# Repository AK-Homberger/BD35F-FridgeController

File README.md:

# BD35F Fridge Controller
An electronic thermostat for a Danfoss/Secop [BD35F](https://assets.danfoss.com/documents/latest/178661/AI376451289296en-000101.pdf) Compressor with ESP8266 (D1 Mini).

The Danfoss/Secop BD35F compressor is a widely used DC powered compressor. I'm using it on my boat to cool the fridge. Unfortunately, the original thermostat was defect. Therfore, I decided to create an electronic alternative that has more features than the standard mechanical one.

## Features:
- Uses ESP8266 (D1 Mini) as processor.
- Dual language support (English/German).
- Easy upload of firmware without Arduino IDE possible.
- Temperature is measured with [DS18B20](https://encrypted-tbn0.gstatic.com/shopping?q=tbn:ANd9GcRNmu3D8hUJPGhuSA7nLRoa413b-gMmKO3SzPfPqZvY6wbsBIp207lLPlJ23y0RRw-2xIi-4CoqkTE98FSd--icjlcXm1W_YQ) sensor.
- Implements a Two-Point with I controller to increase the accuracy.
- Supports variable compressor speeds (2000 - 3500 RPM) to adjust cooling capacity and power consumption.
- Supports Boost function to cool down with more power.
- Supports automatic or manual Defrost routine.
- WLAN support (AP or client mode). Configurable via Wifi Manager.
- Browser interface and MDNS support (http://fridgecontrol.local).
- All parameters are configurable with a browser and stored in flash memory of ESP8266.
- [PCB](https://github.com/AK-Homberger/BD35F-FridgeController/blob/main/BD35F-FridgeController/BD35F-FridgeController-PCB.pdf) layout is available in repository (KiCad) and can be orderd from [Aisler.net](https://aisler.net/p/VBBOGMUR).

## Hardware
The hardware is based on an ESP8266 (D1 Mini) and a few additional parts. The 5 Volt supply voltage for the D1 Mini is created with a [step-down](https://www.reichelt.de/de/de/shop/produkt/dc_dc-wandler_r78e_5_v_500_ma_single-159161) converter. 
The temperature is measuered with a [DS18B20](https://www.analog.com/media/en/technical-documentation/data-sheets/ds18b20.pdf) sensor. The compressor is controlled with an open collector transistor between the connection T and C on the BD35F. 

The BD35F is measuering the current between T and C. C is on GND level and T has a pull-up resistor to 5 Volt. Only a few milliampere are flowing. A small NPN transitor (BC337) is sufficient here. There are two options: T permanently on GND level means 2000 RPM speed. A PWM signal (5 KHz) with a defined duty-cycle is used to set speeds from 2000 to 3500 RPM.

The PCB has three connectors:

### 1. Power 
Connect +/-to 12 Volt to the J1 connector. There is a protection against wrong cabling for +/-.

### 2. DS18B20 Temperature Sensor
Connect the three cables from the DS18B20 to the connector J2. The data line has already the pull-up resistor on the PCB. Red = VDD, Yello = D, Blue = GND.
Place the Sensor in the Fridge in middle highth.

### 3. BD35F Compressor
Connect J3 to the compressor connector. Remove the old thermostat cables and connect the cables C and  T to the compressor. You need appropriate cable shoes for the connection.

## Software
There are two ways to install the software to the D1 Mini. Either you install the Arduino IDE or you direcly flash the BIN-file to the device.

### Arduino IDE
Just [download](https://www.arduino.cc/en/software/) the IDE (version 2.x works well). Then add the Boad URL in preferences: "https://arduino.esp8266.com/stable/package_esp8266com_index.json" and install the Board software in the IDE. Then install the following libraries with the library manager:

- WiFiManager
- ArduinoJson
- OneWire
- DallasTemperature
- Preferences

Then download the sketch from GitHud (Button "Code" and download as ZIP) and extract it. Then move to the [FridgeControl.ino](https://github.com/AK-Homberger/BD35F-FridgeController/blob/main/FridgeControl/FridgeControl.ino) file and open the sketch.
Connect the D1 mini with an USB-Cable to the PC and upload the sketch to the D1 Mini. Later uploads can be done with the OTA function via network.

### NodeMCU-PyFlasher
This works without installation of the IDE. Simply download the [NodeMCU-PyFlasher](https://github.com/nodemcu/nodemcu-firmware/releases) and start it. 

Select appropriate serial port and then move to the bin file in the deownloaded code. Use the seetings as shown for the upload.

## Usage

After upload of the firmware you have to re-power the device to start the [Wifi-Manager](https://github.com/tzapu/WiFiManager) (within 2 minutes after restart). Just look for a new WLAN network with the name "Fridgeconfig_AP" and connect to it, without a password. The browser will start automatically. Then select the network (ssid) you want to connect to and enter the password. 

If you don't configure or press "Exit" the device remain in AP mode with a changed name "Fridgecontrol_AP".

You can use this to test the device without a real network to connect to. But this is an open connection. Don't use this permanently.

To start the web interface enter "http://fridgecontrol.local" in the browser. The interface looks then like this:

The page shows the current fridge temperature, the average temperature, the desired set temperature. Duty cycle shows the percentage of the on time compared to the last on and off time cycle. The values are also shown in minutes (On/Off). The status filed shows the staus of the controller (Auto, On, Off, Boost or Defrost).

With the slidebar and +/- you can modify the the set temperature.

With the buttons you can set the mode:

- Auto: Standard mode to control the temperature.
- ON: Switch on the compressor permanently.
- Off: Switch off the compressor permanently.
- Boost: Cool down for a defined time with a different set point, hysteresis and speed.
- Defrost: Manually start a defrost cycle.
- Set: Opens a settings page.

With the settings page you can control the behaviour of the controller without a need to recompile the code. The following settings are available:

- Language:   0=English 1=German language
- Hysteresis: Sets the Hysteresis/deviation for the two point controller. 2 means +/- 2 K. For a set temperature of 6 that means the temperature will between 4 and 8 degrees.
- RPM:         The desired speed of the compressor. Set as low as possible to reduce power consumption (2000 = 3,5A, 3500 = 7A). "0" means T permanently to GND and 2000 RPM (original mechanical thermostat behaviour).
- AVG Error:   This is the allowed deviation from the average. 0 means the compressor will cool down in every cycle until the average temperature reaches the set temperature. The average temperature is calculated with a low pass filter with K of 1/3600. Means average over about one hour.
- Max          High: The maximum high temperture. The compressor will be switched off, if ths level is reached. Independent of average temperature.
- Max Low:     The maximum low temperture. The compressor will be switched on, if ths level is reached. Independent of average temperature.
- Boost Temp.: Desired temperature for the boost function.
- Boost Hyst.: Hysteresis/deviation for the boost function.
- Boost Time   Time in minutes for the boost function.
- Boost RPM:   Compressor speed for the boost function.
- Max Runtime: Used to detect a needed defrost cycle. If the compressor runs for the defined time, a mandatory defrost cycle will start.
- Defrost Time: Set the time for the defrost cycle. Time depends on local fridge details.

After changes press the "Set" butten. The entered value will be checked against the allowed ranges. If everyting is OK you can use "Back" to go back to the main page.

# Parts
- PCB [Aisler](https://aisler.net/p/VBBOGMUR)
- U1 D1 Mini [Link](https://www.reichelt.de/de/en/d1-mini-esp8266-v3-0-d1-mini-p253978.html?&nbc=1)
- U2 Voltage regulator [Link](https://www.reichelt.de/de/de/shop/produkt/dc_dc-wandler_r78e_5_v_500_ma_single-159161)
- R1 Resistor 1 KOhm [Link](https://www.reichelt.de/de/en/carbon-film-resistor-1-4-w-5-1-0-kilo-ohms-1-4w-1-0k-p1315.html?&trstct=pos_2&nbc=1)
- R2 Resistor 4,7 KOhm [Link](https://www.reichelt.com/de/en/shop/product/carbon_film_resistor_1_4_w_5_4_7_kohm-1425)
- Q1 Transistor BC337 [Link](https://www.reichelt.de/de/en/transistor-to-92-bl-npn-45v-800ma-bc-337-25-dio-p219125.html?&nbc=1)
- D1 Diode 1N4001 [Link](https://www.reichelt.de/de/en/rectifier-diode-do41-50-v-1-a-1n-4001-p1723.html?&nbc=1)
- C1 Condensator 10µF [Link](https://www.reichelt.de/de/de/shop/produkt/tantal-kondensator_10_f_10_35v_rm_2_5-20334)
- J1/J3 Connector 2-pin (*2) [Link](https://www.reichelt.de/de/en/2-pin-terminal-strip-spacing-5-08-akl-101-02-p36605.html?&nbc=1)
- J2 Connector 3-pin [Link](https://www.reichelt.com/de/en/shop/product/3-pin_terminal_strip_spacing_5_08-36606)
- DS18B20 [Link](https://www.reichelt.com/de/en/shop/product/shelly_temperature_sensor_ds18b20-287127)

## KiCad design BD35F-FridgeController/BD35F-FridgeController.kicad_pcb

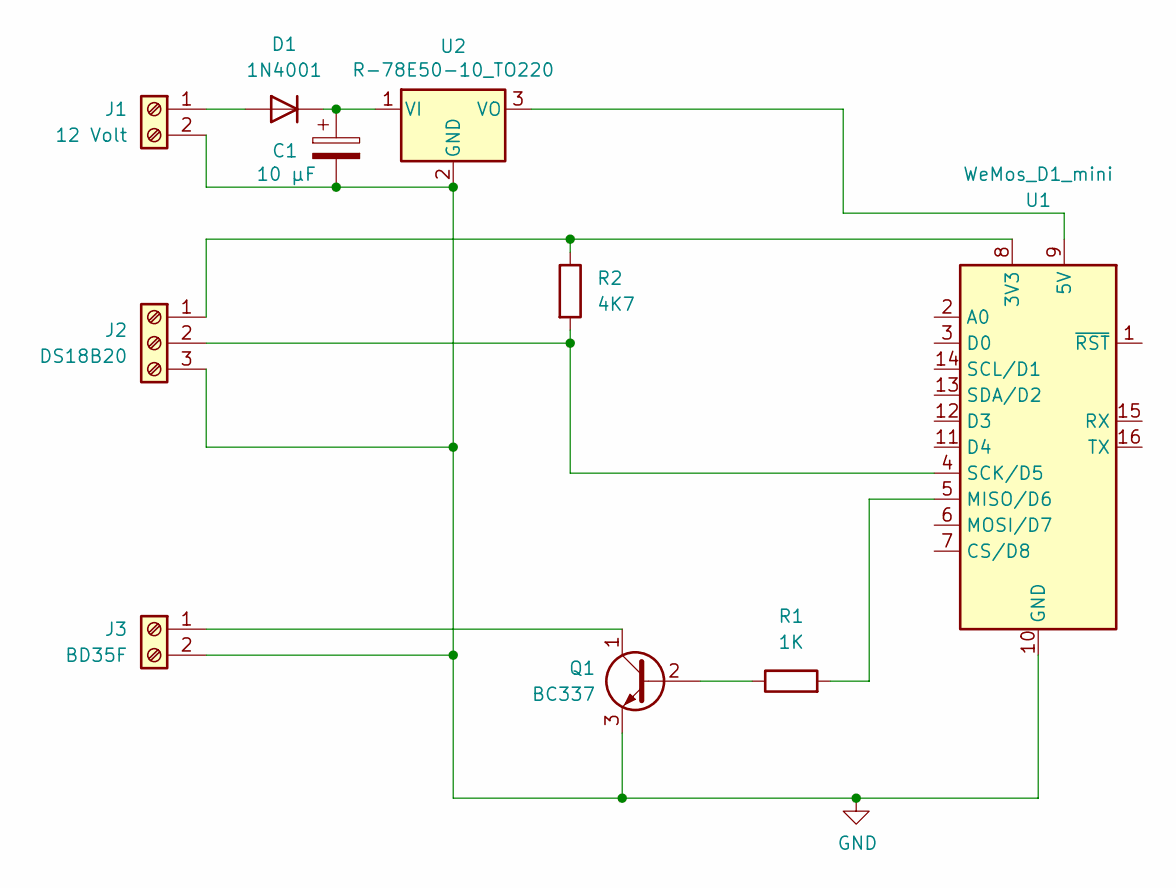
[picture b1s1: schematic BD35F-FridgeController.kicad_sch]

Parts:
C1: 10 µF; CP_Radial_D5.0mm_P2.50mm
D1: 1N4001; D_DO-41_SOD81_P10.16mm_Horizontal
J1: 12 Volt; TerminalBlock_bornier-2_P5.08mm
J2: DS18B20; TerminalBlock_bornier-3_P5.08mm
J3: BD35F; TerminalBlock_bornier-2_P5.08mm
Q1: BC337; TO-92_HandSolder
R1: 1K; R_Axial_DIN0207_L6.3mm_D2.5mm_P10.16mm_Horizontal
R2: 4K7; R_Axial_DIN0207_L6.3mm_D2.5mm_P10.16mm_Horizontal
U1: WeMos_D1_mini; WEMOS_D1_mini_light
U2: R-78E50-10_TO220; TO-220-3_Vertical

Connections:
GND: C1.2, J1.2, J2.3, J3.2, Q1.3 (E), U1.10 (GND), U2.2 (GND)
unnamed: D1.2 (A), J1.1
unnamed: C1.1, D1.1 (K), U2.1 (VI)
unnamed: J2.1, R2.1, U1.8 (3V3)
unnamed: J2.2, R2.2, U1.4 (SCK/D5)
unnamed: J3.1, Q1.1 (C)
unnamed: Q1.2 (B), R1.1
unnamed: U1.9 (5V), U2.3 (VO)
unnamed: R1.2, U1.5 (MISO/D6)

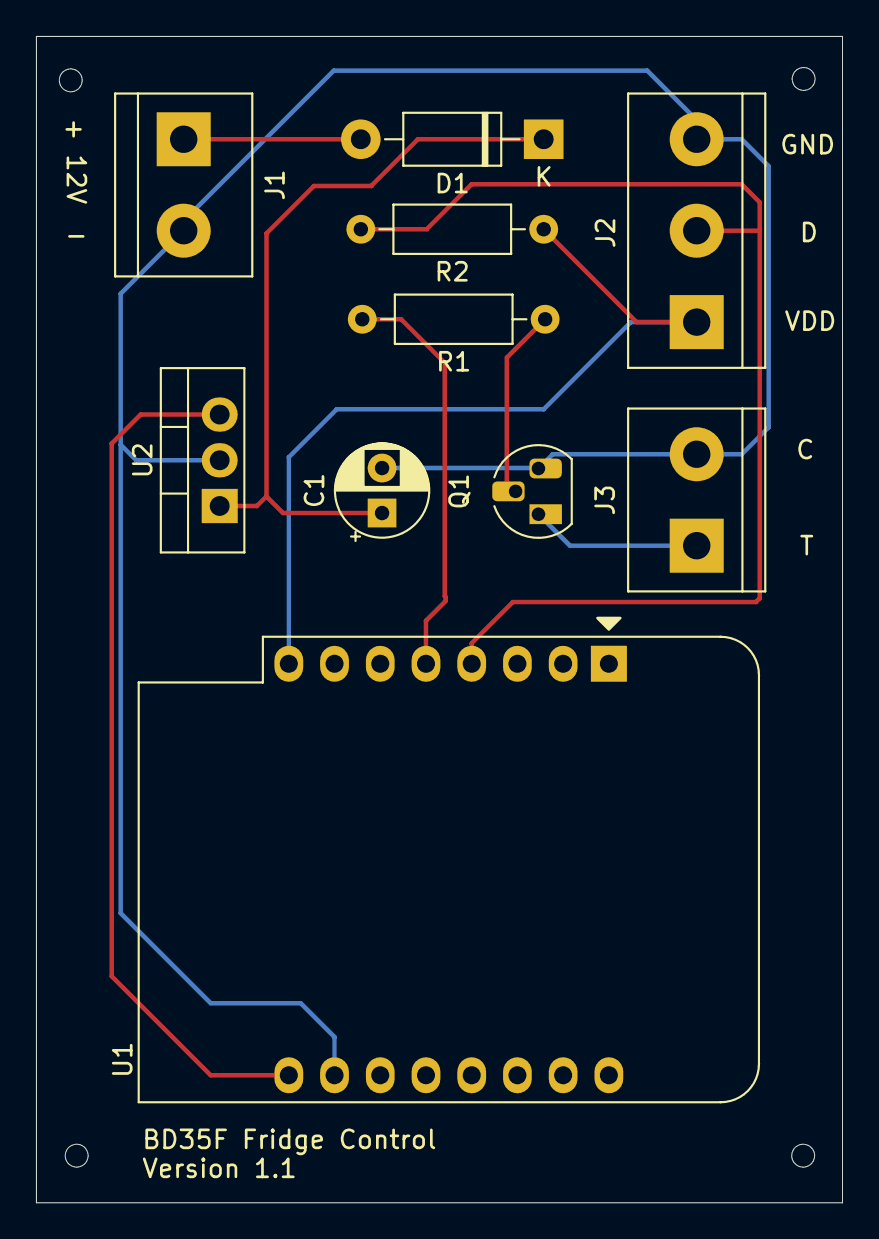
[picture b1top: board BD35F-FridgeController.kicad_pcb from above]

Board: 2 copper layers, 44.8 x 64.8 mm, 10 parts (0 on the bottom side), 9 nets.

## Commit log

2025-10-04 Version 1.1
    Corrected duty cycle calculation (double type instead of unsigned).
